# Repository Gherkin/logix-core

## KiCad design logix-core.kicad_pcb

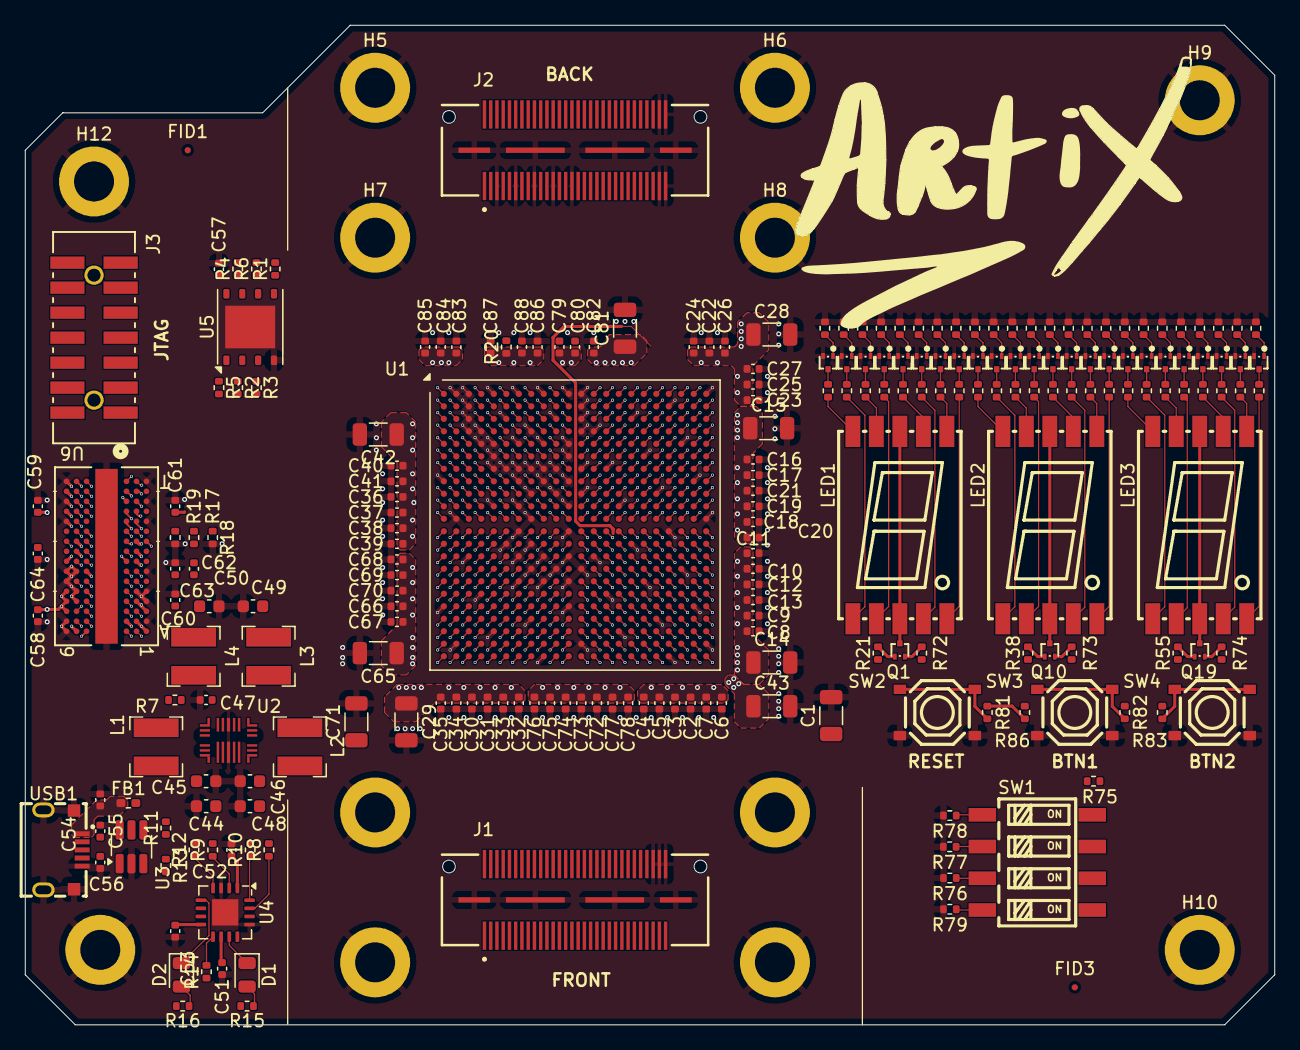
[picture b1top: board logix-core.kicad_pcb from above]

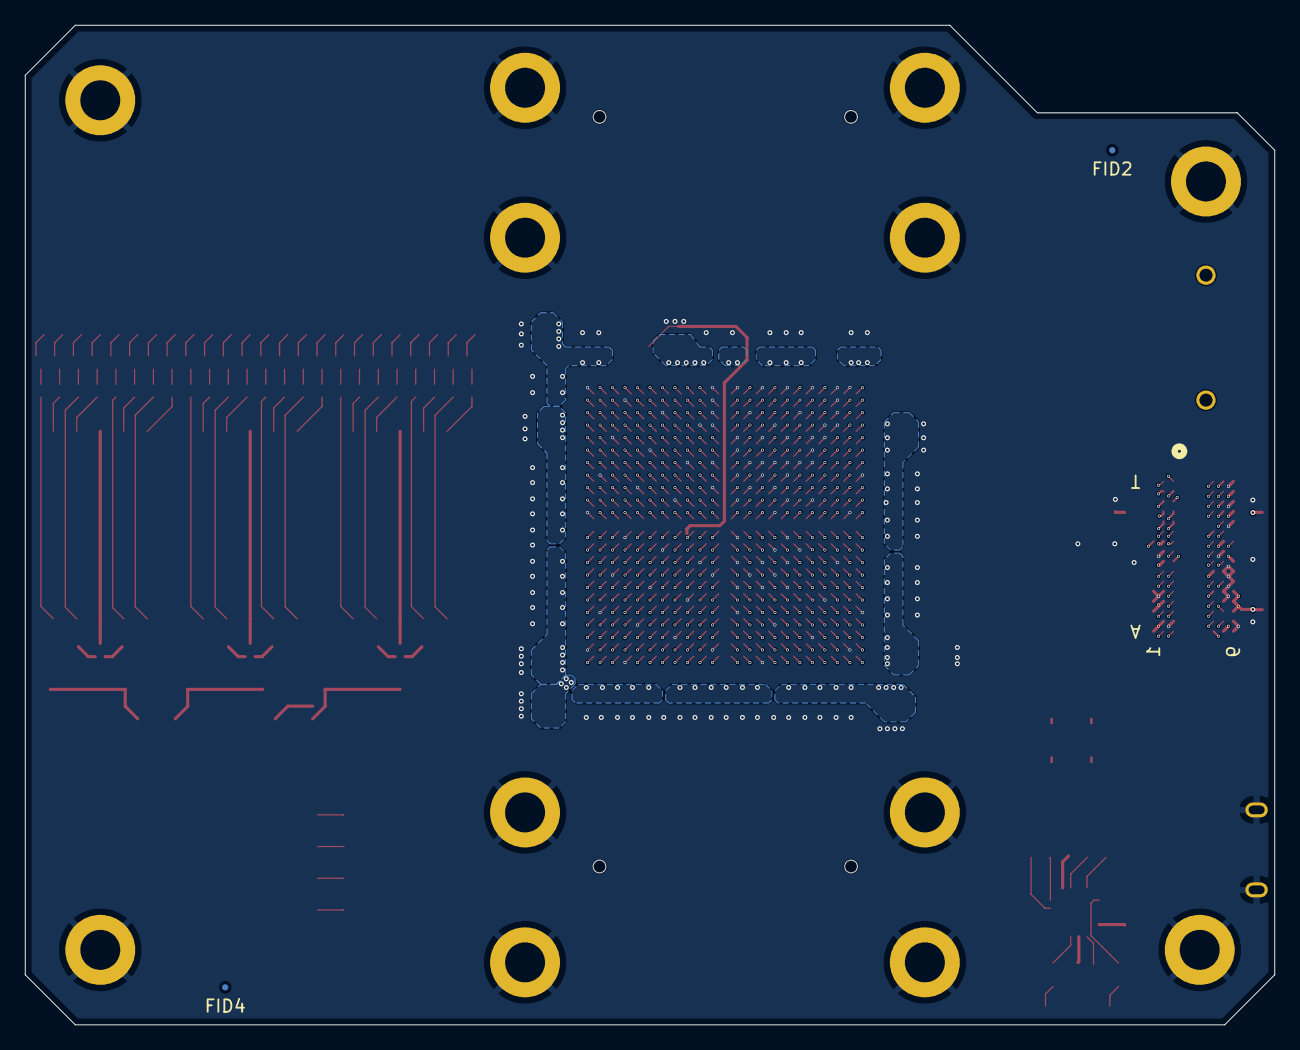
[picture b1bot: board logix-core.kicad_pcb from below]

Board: 6 copper layers, 100.0 x 80.0 mm, 238 parts (2 on the bottom side), 191 nets.

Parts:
C1, C14, C15, C28, C29, C42, C43, C71, C81: 47u; C_1206_3216Metric
C2, C3, C12, C13, C16, C17, C26, C27, C30, C31, C40, C41, C66, C67, C72, C73, C83, C88: 4.7u; C_0402_1005Metric
C4, C5, C6, C7, C8, C9, C10, C11, C18, C19, C20, C21, C22, C23, C24, C25, C32, C33, C34, C35, C36, C37, C38, C39, C68, C69, C70, C74, C75, C76, C77, C78, C79, C82: 0.47u; C_0402_1005Metric
C44, C45, C46, C48, C49, C50: 22u; C_0603_1608Metric
C47, C58, C59, C60, C61, C63: 1u; C_0402_1005Metric
C51, C52, C53, C57, C84, C85, C86, C87: 100n; C_0402_1005Metric
C54, C62, C64, C80: 10n; C_0402_1005Metric
C55, C56: 47p; C_0402_1005Metric
C65: 100u; C_1206_3216Metric
D1, D2: LED; LED_0805_2012Metric
FB1: FerriteBead; R_0402_1005Metric_Pad0.72x0.64mm_HandSolder
FID1, FID2, FID3, FID4: Fiducial; Fiducial_0.5mm_Mask1mm
H1, H2, H3, H4, H5, H6, H7, H8, H9, H10, H11, H12: MountingHole_Pad; MountingHole_3.2mm_M3_DIN965_Pad
J1, J2: QSH-030-01-X-D-A-XX; SAMTEC_QSH-030-01-X-D-A-XX
J3: 878321420; CONN_87832-1420_MOL
L1, L2, L3, L4: 2.2u; L_Bourns-SRN4018
LED1, LED2, LED3: SLS0391FR1A1GD_C2913076; LED-SEG-SMD_10P-L13.0-W9.8-P1.88-S13.70-BL
Q1, Q10, Q19: TPNTK3139PT1G; SOT-723_L1.2-W0.8-P0.40-LS1.2-BR
Q2, Q3, Q4, Q5, Q6, Q7, Q8, Q9, Q11, Q12, Q13, Q14, Q15, Q16, Q17, Q18, Q20, Q21, Q22, Q23, Q24, Q25, Q26, Q27: 2N7002M3T5G-ES; SOT-723_L1.2-W0.8-P0.80-LS1.2-BL
R1, R2, R3, R4, R5, R6, R8, R9, R10, R12, R72, R73, R74, R75, R86: 0; R_0402_1005Metric
R7: 10k; R_0402_1005Metric
R11, R13: 27.4; R_0402_1005Metric
R14, R15, R16, R20: 100; R_0402_1005Metric
R17, R18: 1k; R_0402_1005Metric
R19: 240; R_0402_1005Metric
R21, R30, R31, R32, R33, R34, R35, R36, R37, R38, R47, R48, R49, R50, R51, R52, R53, R54, R55, R64, R65, R66, R67, R68, R69, R70, R71, R76, R77, R78, R79, R81, R82, R83: 100k; R_0402_1005Metric
R22, R23, R24, R25, R26, R27, R28, R29, R39, R40, R41, R42, R43, R44, R45, R46, R56, R57, R58, R59, R60, R61, R62, R63: 68; R_0402_1005Metric
SW1: SMXS-04K-TP; SW-SMD_SMXS-04K-TP
SW2, SW3, SW4: TS-1187A-B-A-B; SW-SMD_4P-L5.1-W5.1-P3.70-LS6.5-TL_H1.5
U1: XC7A35T-FGG484; Xilinx_FGG484
U2: MP5470GL-0000-P; QFN-3x4_MP5470_MNP
U3: TPUSBLC6-4SC6; SOT-23-6_Handsoldering
U4: FT230XQ; QFN-16-1EP_4x4mm_P0.65mm_EP2.1x2.1mm
U5: MX25L3233FZN; WSON-8-1EP_6x5mm_P1.27mm_EP3.4x4mm
U6: MT41K256M16TW-107:P; FBGA96_8X14_MRN
USB1: USB-MR-D-037; MICRO-USB-SMD_DEALON_USB-MR-D-037

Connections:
+1V5: C50.1, C58.1, C59.1, C60.1, C61.1, C62.1, J1.54, J2.54, L4.2, R17.1, U2.18 (FB4), U6.A1 (VDDQ), U6.A8 (VDDQ), U6.B2 (VDD), U6.C1 (VDDQ), U6.C9 (VDDQ), U6.D2 (VDDQ), U6.D9 (VDD), U6.E9 (VDDQ), U6.F1 (VDDQ), U6.G7 (VDD), U6.H2 (VDDQ), U6.H9 (VDDQ), U6.K2 (VDD), U6.K8 (VDD), U6.N1 (VDD), U6.N9 (VDD), U6.R1 (VDD), U6.R9 (VDD)
+1V8: C49.1, J1.52, J2.56, L3.2, U2.10 (FB3)
+3.3V: C48.1, J1.48, J1.50, J2.55, L2.2, R72.1, R73.1, R74.1, R75.1, R86.1, U2.6 (FB2)
/7SEG1/7SEG_A_DRAIN: LED1.3 (COM), LED1.8 (COM), Q1.3 (D)
/7SEG1/7SEG_CA: LED1.7 (A), R22.2
/7SEG1/7SEG_CA_DRAIN: Q2.3 (D), R22.1
/7SEG1/7SEG_CB: LED1.6 (B), R23.2
/7SEG1/7SEG_CB_DRAIN: Q3.3 (D), R23.1
/7SEG1/7SEG_CC: LED1.4 (C), R24.2
/7SEG1/7SEG_CC_DRAIN: Q4.3 (D), R24.1
/7SEG1/7SEG_CD: LED1.2 (D), R25.2
/7SEG1/7SEG_CDP: LED1.5 (DP), R29.2
/7SEG1/7SEG_CDP_DRAIN: Q9.3 (D), R29.1
/7SEG1/7SEG_CD_DRAIN: Q5.3 (D), R25.1
/7SEG1/7SEG_CE: LED1.1 (E), R26.2
/7SEG1/7SEG_CE_DRAIN: Q6.3 (D), R26.1
/7SEG1/7SEG_CF: LED1.9 (F), R27.2
/7SEG1/7SEG_CF_DRAIN: Q7.3 (D), R27.1
/7SEG1/7SEG_CG: LED1.10 (G), R28.2
/7SEG1/7SEG_CG_DRAIN: Q8.3 (D), R28.1
/7SEG1_A: Q1.1 (G), R21.2, U1.P20 (IO_0_14)
/7SEG1_C0: Q2.1 (G), R30.1, U1.P22 (IO_L1P_T0_D00_MOSI_14)
/7SEG1_C1: Q3.1 (G), R31.1, U1.R22 (IO_L1N_T0_D01_DIN_14)
/7SEG1_C2: Q4.1 (G), R32.1, U1.P21 (IO_L2P_T0_D02_14)
/7SEG1_C3: Q5.1 (G), R33.1, U1.R21 (IO_L2N_T0_D03_14)
/7SEG1_C4: Q6.1 (G), R34.1, U1.U22 (IO_L3P_T0_DQS_PUDC_B_14)
/7SEG1_C5: Q7.1 (G), R35.1, U1.V22 (IO_L3N_T0_DQS_EMCCLK_14)
/7SEG1_C6: Q8.1 (G), R36.1, U1.T21 (IO_L4P_T0_D04_14)
/7SEG1_C7: Q9.1 (G), R37.1, U1.U21 (IO_L4N_T0_D05_14)
/7SEG2/7SEG_A_DRAIN: LED2.3 (COM), LED2.8 (COM), Q10.3 (D)
/7SEG2/7SEG_CA: LED2.7 (A), R39.2
/7SEG2/7SEG_CA_DRAIN: Q11.3 (D), R39.1
/7SEG2/7SEG_CB: LED2.6 (B), R40.2
/7SEG2/7SEG_CB_DRAIN: Q12.3 (D), R40.1
/7SEG2/7SEG_CC: LED2.4 (C), R41.2
/7SEG2/7SEG_CC_DRAIN: Q13.3 (D), R41.1
/7SEG2/7SEG_CD: LED2.2 (D), R42.2
/7SEG2/7SEG_CDP: LED2.5 (DP), R46.2
/7SEG2/7SEG_CDP_DRAIN: Q18.3 (D), R46.1
/7SEG2/7SEG_CD_DRAIN: Q14.3 (D), R42.1
/7SEG2/7SEG_CE: LED2.1 (E), R43.2
/7SEG2/7SEG_CE_DRAIN: Q15.3 (D), R43.1
/7SEG2/7SEG_CF: LED2.9 (F), R44.2
/7SEG2/7SEG_CF_DRAIN: Q16.3 (D), R44.1
/7SEG2/7SEG_CG: LED2.10 (G), R45.2
/7SEG2/7SEG_CG_DRAIN: Q17.3 (D), R45.1
/7SEG2_A: Q10.1 (G), R38.2, U1.P19 (IO_L5P_T0_D06_14)
/7SEG2_C0: Q11.1 (G), R47.1, U1.R19 (IO_L5N_T0_D07_14)
/7SEG2_C1: Q12.1 (G), R48.1, U1.T19 (IO_L6P_T0_FCS_B_14)
/7SEG2_C2: Q13.1 (G), R49.1, U1.T20 (IO_L6N_T0_D08_VREF_14)
/7SEG2_C3: Q14.1 (G), R50.1, U1.W21 (IO_L7P_T1_D09_14)
/7SEG2_C4: Q15.1 (G), R51.1, U1.W22 (IO_L7N_T1_D10_14)
/7SEG2_C5: Q16.1 (G), R52.1, U1.AA20 (IO_L8P_T1_D11_14)
/7SEG2_C6: Q17.1 (G), R53.1, U1.AA21 (IO_L8N_T1_D12_14)
/7SEG2_C7: Q18.1 (G), R54.1, U1.Y21 (IO_L9P_T1_DQS_14)
/7SEG3/7SEG_A_DRAIN: LED3.3 (COM), LED3.8 (COM), Q19.3 (D)
/7SEG3/7SEG_CA: LED3.7 (A), R56.2
/7SEG3/7SEG_CA_DRAIN: Q20.3 (D), R56.1
/7SEG3/7SEG_CB: LED3.6 (B), R57.2
/7SEG3/7SEG_CB_DRAIN: Q21.3 (D), R57.1
/7SEG3/7SEG_CC: LED3.4 (C), R58.2
/7SEG3/7SEG_CC_DRAIN: Q22.3 (D), R58.1
/7SEG3/7SEG_CD: LED3.2 (D), R59.2
/7SEG3/7SEG_CDP: LED3.5 (DP), R63.2
/7SEG3/7SEG_CDP_DRAIN: Q27.3 (D), R63.1
/7SEG3/7SEG_CD_DRAIN: Q23.3 (D), R59.1
/7SEG3/7SEG_CE: LED3.1 (E), R60.2
/7SEG3/7SEG_CE_DRAIN: Q24.3 (D), R60.1
/7SEG3/7SEG_CF: LED3.9 (F), R61.2
/7SEG3/7SEG_CF_DRAIN: Q25.3 (D), R61.1
/7SEG3/7SEG_CG: LED3.10 (G), R62.2
/7SEG3/7SEG_CG_DRAIN: Q26.3 (D), R62.1
/7SEG3_A: Q19.1 (G), R55.2, U1.V20 (IO_L11N_T1_SRCC_14)
/7SEG3_C0: Q20.1 (G), R64.1, U1.W19 (IO_L12P_T1_MRCC_14)
/7SEG3_C1: Q21.1 (G), R65.1, U1.W20 (IO_L12N_T1_MRCC_14)
/7SEG3_C2: Q22.1 (G), R66.1, U1.Y18 (IO_L13P_T2_MRCC_14)
/7SEG3_C3: Q23.1 (G), R67.1, U1.Y19 (IO_L13N_T2_MRCC_14)
/7SEG3_C4: Q24.1 (G), R68.1, U1.V18 (IO_L14P_T2_SRCC_14)
/7SEG3_C5: Q25.1 (G), R69.1, U1.V19 (IO_L14N_T2_SRCC_14)
/7SEG3_C6: Q26.1 (G), R70.1, U1.AA19 (IO_L15P_T2_DQS_RDWR_B_14)
/7SEG3_C7: Q27.1 (G), R71.1, U1.AB20 (IO_L15N_T2_DQS_DOUT_CSO_B_14)
/BTN1#: R82.2, SW3.3 (C), SW3.4 (D)
/BTN2#: R83.2, SW4.3 (C), SW4.4 (D)
/DDR3/DDR_VREF: C62.2, C63.1, C64.1, R17.2, R18.1, U6.H1 (VREFDQ), U6.M8 (VREFCA)
/DDR3/ZQ: R19.1, U6.L8 (ZQ)
/DDR3_ADDR0: U1.J2 (IO_L9N_T1_DQS_AD7N_35), U6.N3 (A0)
/DDR3_ADDR1: U1.K2 (IO_L9P_T1_DQS_AD7P_35), U6.P7 (A1)
/DDR3_ADDR2: U1.G2 (IO_L8N_T1_AD14N_35), U6.P3 (A2)
/DDR3_ADDR3: U1.H2 (IO_L8P_T1_AD14P_35), U6.N2 (A3)
/DDR3_ADDR4: U1.J1 (IO_L7N_T1_AD6N_35), U6.P8 (A4)
/DDR3_ADDR5: U1.K1 (IO_L7P_T1_AD6P_35), U6.P2 (A5)
/DDR3_ADDR6: U1.F3 (IO_L6P_T0_35), U6.R8 (A6)
/DDR3_ADDR7: U1.F1 (IO_L5N_T0_AD13N_35), U6.R2 (A7)
/DDR3_ADDR8: U1.G1 (IO_L5P_T0_AD13P_35), U6.T8 (A8)
/DDR3_ADDR9: U1.D2 (IO_L4N_T0_35), U6.R3 (A9)
/DDR3_ADDR10: U1.E2 (IO_L4P_T0_35), U6.L7 (A10/AP)
/DDR3_ADDR11: U1.B2 (IO_L2N_T0_AD12N_35), U6.R7 (A11)
/DDR3_ADDR12: U1.C2 (IO_L2P_T0_AD12P_35), U6.N7 (A12/*BC)
/DDR3_ADDR13: U1.A1 (IO_L1N_T0_AD4N_35), U6.T3 (A13)
/DDR3_ADDR14: U1.B1 (IO_L1P_T0_AD4P_35), U6.T7 (A14)
/DDR3_BLOCK_ADDR0: U1.H3 (IO_L11P_T1_SRCC_35), U6.M2 (BA0)
/DDR3_BLOCK_ADDR1: U1.H5 (IO_L10N_T1_AD15N_35), U6.N8 (BA1)
/DDR3_BLOCK_ADDR2: U1.J5 (IO_L10P_T1_AD15P_35), U6.M3 (BA2)
/DDR3_CAS#: U1.H4 (IO_L12P_T1_MRCC_35), U6.K3 (*CAS)
/DDR3_CLK+: U1.E1 (IO_L3P_T0_DQS_AD5P_35), U6.J7 (CK)
/DDR3_CLK-: U1.D1 (IO_L3N_T0_DQS_AD5N_35), U6.K7 (*CK)
/DDR3_CLK_EN: U1.L1 (IO_L15N_T2_DQS_35), U6.K9 (CKE)
/DDR3_CS#: U1.M1 (IO_L15P_T2_DQS_35), U6.L2 (*CS)
/DDR3_DQ0: U1.R1 (IO_L20P_T3_35), U6.E3 (DQ0)
/DDR3_DQ1: U1.P1 (IO_L20N_T3_35), U6.F7 (DQ1)
/DDR3_DQ2: U1.P2 (IO_L22P_T3_35), U6.F2 (DQ2)
/DDR3_DQ3: U1.N2 (IO_L22N_T3_35), U6.F8 (DQ3)
/DDR3_DQ4: U1.M6 (IO_L23P_T3_35), U6.H3 (DQ4)
/DDR3_DQ5: U1.M5 (IO_L23N_T3_35), U6.H8 (DQ5)
/DDR3_DQ6: U1.P6 (IO_L24P_T3_35), U6.G2 (DQ6)
/DDR3_DQ7: U1.N5 (IO_L24N_T3_35), U6.H7 (DQ7)
/DDR3_DQ8: U1.U1 (IO_L1N_T0_34), U6.D7 (DQ8)
/DDR3_DQ9: U1.U2 (IO_L2P_T0_34), U6.C3 (DQ9)
/DDR3_DQ10: U1.V2 (IO_L2N_T0_34), U6.C8 (DQ10)
/DDR3_DQ11: U1.W2 (IO_L4P_T0_34), U6.C2 (DQ11)
/DDR3_DQ12: U1.Y2 (IO_L4N_T0_34), U6.A7 (DQ12)
/DDR3_DQ13: U1.W1 (IO_L5P_T0_34), U6.A2 (DQ13)
/DDR3_DQ14: U1.Y1 (IO_L5N_T0_34), U6.B8 (DQ14)
/DDR3_DQ15: U1.U3 (IO_L6P_T0_34), U6.A3 (DQ15)
/DDR3_LDM: U1.N4 (IO_L19P_T3_35), U6.E7 (LDM)
/DDR3_LDQS+: U1.P5 (IO_L21P_T3_DQS_35), U6.F3 (LDQS)
/DDR3_LDQS-: U1.P4 (IO_L21N_T3_DQS_35), U6.G3 (*LDQS)
/DDR3_ODT: U1.M3 (IO_L16P_T2_35), U6.K1 (ODT)
/DDR3_RAS#: U1.G3 (IO_L11N_T1_SRCC_35), U6.J3 (*RAS)
/DDR3_RESET#: U1.K4 (IO_L13P_T2_MRCC_35), U6.T2 (*RESET)
/DDR3_UDM: U1.T1 (IO_L1P_T0_34), U6.D3 (UDM)
/DDR3_UDQS+: U1.R3 (IO_L3P_T0_DQS_34), U6.C7 (UDQS)
/DDR3_UDQS-: U1.R2 (IO_L3N_T0_DQS_34), U6.B7 (*UDQS)
/DDR3_WE#: U1.G4 (IO_L12N_T1_MRCC_35), U6.L3 (*WE)
/DIP_SW0: R78.1, SW1.1
/DIP_SW1: R77.1, SW1.2
/DIP_SW2: R76.1, SW1.3
/DIP_SW3: R79.1, SW1.4
/DIP_SWITCH/BTN_VCC: R81.1, R82.1, R83.1, R86.2
/DIP_SWITCH/DIP_VCC: R75.2, SW1.5, SW1.6, SW1.7, SW1.8
/FLASH_SPI.CS#: R5.1, U5.1 (~CS)
/FLASH_SPI.D0: R1.1, U5.5 (SI/SIO0)
/FLASH_SPI.D1: R2.1, U5.2 (SO/SIO1)
/FLASH_SPI.D2: R3.1, U5.3 (~WP/SIO2)
/FLASH_SPI.D3: R4.1, U5.7 (~HOLD/SIO3)
/FPGA/FPGA pg.1/VCCO13: C1.1, C2.1, C3.1, C4.1, C5.1, C6.1, C7.1, U1.AA17 (VCCO_13), U1.AB14 (VCCO_13), U1.V16 (VCCO_13), U1.W13 (VCCO_13), U1.Y10 (VCCO_13)
/FPGA/FPGA pg.1/VCCO14: C8.1, C9.1, C10.1, C11.1, C12.1, C13.1, C14.1, U1.M14 (VCCO_14), U1.P18 (VCCO_14), U1.R15 (VCCO_14), U1.T22 (VCCO_14), U1.U19 (VCCO_14), U1.Y20 (VCCO_14)
/FPGA/FPGA pg.2/VCCO15: C15.1, C16.1, C17.1, C18.1, C19.1, C20.1, C21.1, U1.G19 (VCCO_15), U1.H16 (VCCO_15), U1.J13 (VCCO_15), U1.K20 (VCCO_15), U1.L17 (VCCO_15), U1.N21 (VCCO_15)
/FPGA/FPGA pg.2/VCCO16: C22.1, C23.1, C24.1, C25.1, C26.1, C27.1, C28.1, U1.A17 (VCCO_16), U1.B14 (VCCO_16), U1.C21 (VCCO_16), U1.D18 (VCCO_16), U1.E15 (VCCO_16), U1.F22 (VCCO_16)
/FPGA/FPGA pg.3/VCCO34: C29.1, C30.1, C31.1, C32.1, C33.1, C34.1, C35.1, U1.AA7 (VCCO_34), U1.AB4 (VCCO_34), U1.R5 (VCCO_34), U1.T2 (VCCO_34), U1.V6 (VCCO_34), U1.W3 (VCCO_34)
/FPGA/FPGA pg.3/VCCO35: C36.1, C37.1, C38.1, C39.1, C40.1, C41.1, C42.1, U1.C1 (VCCO_35), U1.F2 (VCCO_35), U1.H6 (VCCO_35), U1.J3 (VCCO_35), U1.M4 (VCCO_35), U1.N1 (VCCO_35)
/FPGA/FPGA pg.4/INT_FLASH_SPI_CLK: R6.2, U1.L12 (CCLK_0)
/FPGA/FPGA pg.4/VCCO_0: C43.1, U1.F12 (VCCO_0), U1.T12 (VCCO_0)
/FPGA/FPGA pg.5/MGTAVCC: C83.1, C84.1, C85.1, U1.D6 (MGTAVCC), U1.D10 (MGTAVCC), U1.E8 (MGTAVCC), U1.F7 (MGTAVCC), U1.F9 (MGTAVCC)
/FPGA/FPGA pg.5/MGTAVTT: C86.1, C87.1, C88.1, R20.1, U1.B5 (MGTAVTT), U1.B7 (MGTAVTT), U1.B9 (MGTAVTT), U1.B11 (MGTAVTT), U1.C4 (MGTAVTT), U1.C8 (MGTAVTT)
/FPGA/FPGA pg.5/VCCADC: C79.1, C80.1, U1.K10 (VCCADC_0)
/FPGA/FPGA pg.5/VCCAUX: C71.1, C72.1, C73.1, C74.1, C75.1, C76.1, C77.1, C78.1, U1.E12 (VCCBATT_0), U1.H12 (VCCAUX), U1.K12 (VCCAUX), U1.M12 (VCCAUX), U1.P12 (VCCAUX), U1.R11 (VCCAUX)
/FPGA/FPGA pg.5/VCCBRAM: C81.1, C82.1, U1.J11 (VCCBRAM), U1.L11 (VCCBRAM), U1.N11 (VCCBRAM)
/FPGA/FPGA pg.5/VCCINT: C65.1, C66.1, C67.1, C68.1, C69.1, C70.1, U1.H8 (VCCINT), U1.H10 (VCCINT), U1.J7 (VCCINT), U1.J9 (VCCINT), U1.K8 (VCCINT), U1.L7 (VCCINT), U1.M8 (VCCINT), U1.N7 (VCCINT), U1.P8 (VCCINT), U1.P10 (VCCINT), U1.R7 (VCCINT), U1.R9 (VCCINT), U1.T8 (VCCINT), U1.T10 (VCCINT)
/RST_BTN#: R81.2, SW2.3 (C), SW2.4 (D)
/USB/EXT_USB_D+: C56.1, R13.1, U3.1, USB1.3 (D+)
/USB/EXT_USB_D-: C55.1, R11.1, U3.6, USB1.2 (D-)
/USB/EXT_VBUS: C54.1, FB1.1, USB1.1 (VCC)
/USB/FTDI_CBUS1: D1.1 (K), U4.11 (CBUS1)
/USB/FTDI_CBUS2: D2.1 (K), U4.5 (CBUS2)
/USB/FTDI_CTS#: R12.1, U4.4 (~CTS)
/USB/FTDI_RTS#: R10.1, U4.16 (~RTS)
/USB/FTDI_RXD: R9.1, U4.2 (RXD)
/USB/FTDI_TXD: R8.1, U4.15 (TXD)
/USB/USB_D+: R13.2, U4.6 (USBDP)
/USB/USB_D-: R11.2, U4.7 (USBDM)
AGND: C80.2, U1.K9 (GNDADC_0)
GND: C1.2, C2.2, C3.2, C4.2, C5.2, C6.2, C7.2, C8.2, C9.2, C10.2, C11.2, C12.2, C13.2, C14.2, C15.2, C16.2, C17.2, C18.2, C19.2, C20.2, C21.2, C22.2, C23.2, C24.2, C25.2, C26.2, C27.2, C28.2, C29.2, C30.2, C31.2, C32.2, C33.2, C34.2, C35.2, C36.2, C37.2, C38.2, C39.2, C40.2, C41.2, C42.2, C43.2, C44.2, C45.2, C46.2, C47.2, C48.2, C49.2, C50.2, C51.2, C52.2, C53.2, C54.2, C55.2, C56.2, C57.2, C58.2, C59.2, C60.2, C61.2, C63.2, C64.2, C65.2, C66.2, C67.2, C68.2, C69.2, C70.2, C71.2, C72.2, C73.2, C74.2, C75.2, C76.2, C77.2, C78.2, C79.2, C81.2, C82.2, C83.2, C84.2, C85.2, C86.2, C87.2, C88.2, H1.1, H2.1, H3.1, H4.1, H5.1, H6.1, H7.1, H8.1, H9.1, H10.1, H11.1, H12.1, J1.56, J1.58, J1.60, J1.G1, J1.G2, J1.G3, J1.G4, J2.05, J2.11, J2.17, J2.23, J2.29, J2.57, J2.58, J2.59, J2.60, J2.G1, J2.G2, J2.G3, J2.G4, Q2.2 (S), Q3.2 (S), Q4.2 (S), Q5.2 (S), Q6.2 (S), Q7.2 (S), Q8.2 (S), Q9.2 (S), Q11.2 (S), Q12.2 (S), Q13.2 (S), Q14.2 (S), Q15.2 (S), Q16.2 (S), Q17.2 (S), Q18.2 (S), Q20.2 (S), Q21.2 (S), Q22.2 (S), Q23.2 (S), Q24.2 (S), Q25.2 (S), Q26.2 (S), Q27.2 (S), R18.2, R19.2, R30.2, R31.2, R32.2, R33.2, R34.2, R35.2, R36.2, R37.2, R47.2, R48.2, R49.2, R50.2, R51.2, R52.2, R53.2, R54.2, R64.2, R65.2, R66.2, R67.2, R68.2, R69.2, R70.2, R71.2, R76.2, R77.2, R78.2, R79.2, SW2.1 (A), SW2.2 (B), SW3.1 (A), SW3.2 (B), SW4.1 (A), SW4.2 (B), U1.A2 (GND), U1.A3 (GND), U1.A5 (GND), U1.A7 (GND), U1.A9 (GND), U1.A11 (GND), U1.A12 (GND), U1.A22 (GND), U1.AA2 (GND), U1.AA12 (GND), U1.AA22 (GND), U1.AB9 (GND), U1.AB19 (GND), U1.B3 (GND), U1.B12 (GND), U1.B19 (GND), U1.C3 (GND), U1.C6 (GND), U1.C10 (GND), U1.C12 (GND), U1.C16 (GND), U1.D3 (GND), U1.D4 (GND), U1.D8 (GND), U1.D12 (GND), U1.D13 (GND), U1.E4 (GND), U1.E5 (GND), U1.E7 (GND), U1.E9 (GND), U1.E11 (GND), U1.E20 (GND), U1.F5 (GND), U1.F11 (GND), U1.F17 (GND), U1.G5 (GND), U1.G6 (GND), U1.G7 (GND), U1.G8 (GND), U1.G9 (GND), U1.G10 (GND), U1.G12 (GND), U1.G14 (GND), U1.H1 (GND), U1.H7 (GND), U1.H9 (GND), U1.H11 (GND), U1.H21 (GND), U1.J8 (GND), U1.J10 (GND), U1.J12 (GND), U1.J18 (GND), U1.K5 (GND), U1.K7 (GND), U1.K11 (GND), U1.K15 (GND), U1.L2 (GND), U1.L8 (GND), U1.L22 (GND), U1.M7 (GND), U1.M11 (GND), U1.M19 (GND), U1.N6 (GND), U1.N8 (GND), U1.N16 (GND), U1.P3 (GND), U1.P7 (GND), U1.P9 (GND), U1.P11 (GND), U1.P13 (GND), U1.R8 (GND), U1.R10 (GND), U1.R12 (GND), U1.R20 (GND), U1.T7 (GND), U1.T9 (GND), U1.T11 (GND), U1.T17 (GND), U1.U4 (GND), U1.U14 (GND), U1.V1 (GND), U1.V11 (GND), U1.V21 (GND), U1.W8 (GND), U1.W18 (GND), U1.Y5 (GND), U1.Y15 (GND), U2.3 (GND), U2.9 (SGND2), U2.14 (GND), U2.19 (AGND), U2.21 (SGND1), U3.2 (VSS), U4.3 (GND), U4.13 (GND), U4.17 (GND), U5.4 (GND), U5.9 (EP), U6.97 (EPAD), U6.A9 (VSS), U6.B1 (VSSQ), U6.B3 (VSS), U6.B9 (VSSQ), U6.D1 (VSSQ), U6.D8 (VSSQ), U6.E1 (VSS), U6.E2 (VSSQ), U6.E8 (VSSQ), U6.F9 (VSSQ), U6.G1 (VSSQ), U6.G8 (VSS), U6.G9 (VSSQ), U6.J2 (VSS), U6.J8 (VSS), U6.M1 (VSS), U6.M9 (VSS), U6.P1 (VSS), U6.P9 (VSS), U6.T1 (VSS), U6.T9 (VSS), USB1.5 (GND), USB1.6, USB1.7, USB1.8, USB1.9
unnamed: D1.2 (A), R15.1
unnamed: D2.2 (A), R16.1
unnamed: Q1.2 (S), R21.1, R72.2
unnamed: Q10.2 (S), R38.1, R73.2
unnamed: Q19.2 (S), R55.1, R74.2
unnamed: R20.2, U1.F8 (MGTRREF_216)
unnamed: R7.2, U2.20 (GPIO)
unnamed: L1.1, U2.2 (SW1)
unnamed: L2.1, U2.4 (SW2)
unnamed: L3.1, U2.13 (SW3)
unnamed: L4.1, U2.15 (SW4)
unnamed: C47.1, R7.1, U2.16 (VCC)
unnamed: C53.1, U4.8 (3V3OUT)
unnamed: C52.1, U4.1 (VCCIO)
unnamed: R14.2, U4.9 (~RESET)
unnamed: C57.1, U5.8 (VCC)
VBUS: C45.1, C46.1, C51.1, FB1.2, J1.44, J1.46, J2.49, J2.51, J2.53, U2.1 (VIN1), U2.5 (VIN2), U3.5, U4.10 (VCC)
VCCINT: C44.1, L1.2, U2.22 (FB1)

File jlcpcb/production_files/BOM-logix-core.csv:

Comment,Designator,Footprint,LCSC,Quantity
240,R19,R_0402_1005Metric,C114755,1
1k,"R17,R18",R_0402_1005Metric,C11702,2
FT230XQ,U4,QFN-16-1EP_4x4mm_P0.65mm_EP2.1x2.1mm,C128629,1
100u,C65,C_1206_3216Metric,C15008,1
10n,"C54,C62,C64,C80",C_0402_1005Metric,C15195,4
XC7A35T-FGG484,U1,Xilinx_FGG484,C1521727,1
100n,"C51,C52,C53,C57,C84,C85,C86,C87",C_0402_1005Metric,C1525,8
47p,"C55,C56",C_0402_1005Metric,C1567,2
68,"R22,R23,R24,R25,R26,R27,R28,R29,R39,R40,R41,R42,R43,R44,R45,R46,R56,R57,R58,R59,R60,R61,R62,R63",R_0402_1005Metric,C163455,24
0,"R1,R10,R12,R2,R3,R4,R5,R6,R72,R73,R74,R75,R8,R86,R9",R_0402_1005Metric,C17168,15
27.4,"R11,R13",R_0402_1005Metric,C226391,2
LED,"D1,D2",LED_0805_2012Metric,C2297,2
4.7u,"C12,C13,C16,C17,C2,C26,C27,C3,C30,C31,C40,C41,C66,C67,C72,C73,C83,C88",C_0402_1005Metric,C23733,18
100,"R14,R15,R16,R20",R_0402_1005Metric,C25076,4
100k,"R21,R30,R31,R32,R33,R34,R35,R36,R37,R38,R47,R48,R49,R50,R51,R52,R53,R54,R55,R64,R65,R66,R67,R68,R69,R70,R71,R76,R77,R78,R79,R81,R82,R83",R_0402_1005Metric,C25741,34
10k,R7,R_0402_1005Metric,C25744,1
MT41K256M16TW-107:P,U6,FBGA96_8X14_MRN,C2803004,1
SLS0391FR1A1GD_C2913076,"LED1,LED2,LED3",LED-SEG-SMD_10P-L13.0-W9.8-P1.88-S13.70-BL,C2913076,3
USB-MR-D-037,USB1,MICRO-USB-SMD_DEALON_USB-MR-D-037,C2927008,1
TS-1187A-B-A-B,"SW2,SW3,SW4",SW-SMD_4P-L5.1-W5.1-P3.70-LS6.5-TL_H1.5,C318884,3
0.47u,"C10,C11,C18,C19,C20,C21,C22,C23,C24,C25,C32,C33,C34,C35,C36,C37,C38,C39,C4,C5,C6,C68,C69,C7,C70,C74,C75,C76,C77,C78,C79,C8,C82,C9",C_0402_1005Metric,C47339,34
878321420,J3,CONN_87832-1420_MOL,C492354,1
2N7002M3T5G-ES,"Q11,Q12,Q13,Q14,Q15,Q16,Q17,Q18,Q2,Q20,Q21,Q22,Q23,Q24,Q25,Q26,Q27,Q3,Q4,Q5,Q6,Q7,Q8,Q9",SOT-723_L1.2-W0.8-P0.80-LS1.2-BL,C5224234,24
1u,"C47,C58,C59,C60,C61,C63",C_0402_1005Metric,C52923,6
SMXS-04K-TP,SW1,SW-SMD_SMXS-04K-TP,C5439763,1
TPUSBLC6-4SC6,U3,SOT-23-6_Handsoldering,C558419,1
TPNTK3139PT1G,"Q1,Q10,Q19",SOT-723_L1.2-W0.8-P0.40-LS1.2-BR,C558623,3
QSH-030-01-X-D-A-XX,"J1,J2",SAMTEC_QSH-030-01-X-D-A-XX,C5714556,2
22u,"C44,C45,C46,C48,C49,C50",C_0603_1608Metric,C59461,6
FerriteBead,FB1,R_0402_1005Metric_Pad0.72x0.64mm_HandSolder,C85813,1
2.2u,"L1,L2,L3,L4",L_Bourns-SRN4018,C913207,4
47u,"C1,C14,C15,C28,C29,C42,C43,C71,C81",C_1206_3216Metric,C96123,9
MP5470GL-0000-P,U2,QFN-3x4_MP5470_MNP,,1
MX25L3233FZN,U5,WSON-8-1EP_6x5mm_P1.27mm_EP3.4x4mm,,1

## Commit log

2024-09-15 stuff
2024-09-15 more stuff!
2024-09-15 bit more
2024-09-15 more stuff
2024-09-28 changed ftg256 to csg325, wanted xc7a12t but couldnt find
2024-09-28 started mapping data input pins
2025-02-23 working on ddr3
2025-02-24 working on ddr3 pcb
2025-02-27 working for ddr3 pcb part 2
2025-02-28 more ddr3, rules and stuff
2025-03-01 more ddr3
2025-03-01 wip rickard
2025-03-01 changed ddr3 pinning according to hard-ip in vivado
2025-03-01 changed die to pad length for ddr3
2025-03-01 did preliminary routing on ddr3, fixed clearance rule
2025-03-02 placed decoupling caps for fpga
2025-03-02 more power-work, vccint needs to be moved to left side still
2025-03-02 started looking at ddr3 addr
2025-03-05 started changing package, added correct decoupling
2025-03-05 connected almost all ddr3 pins, started placing decoupling caps
2025-03-19 filled out back connector, finished ddr pinning according to vivado
2025-03-23 added a lot of stuff
2025-03-23 started doing some general floorplanning and outline
2025-03-23 more floorplanning
2025-03-23 did alot of stuff
2025-03-24 did a bit of ddr routing
2025-03-26 did alot of ddr3 routing
